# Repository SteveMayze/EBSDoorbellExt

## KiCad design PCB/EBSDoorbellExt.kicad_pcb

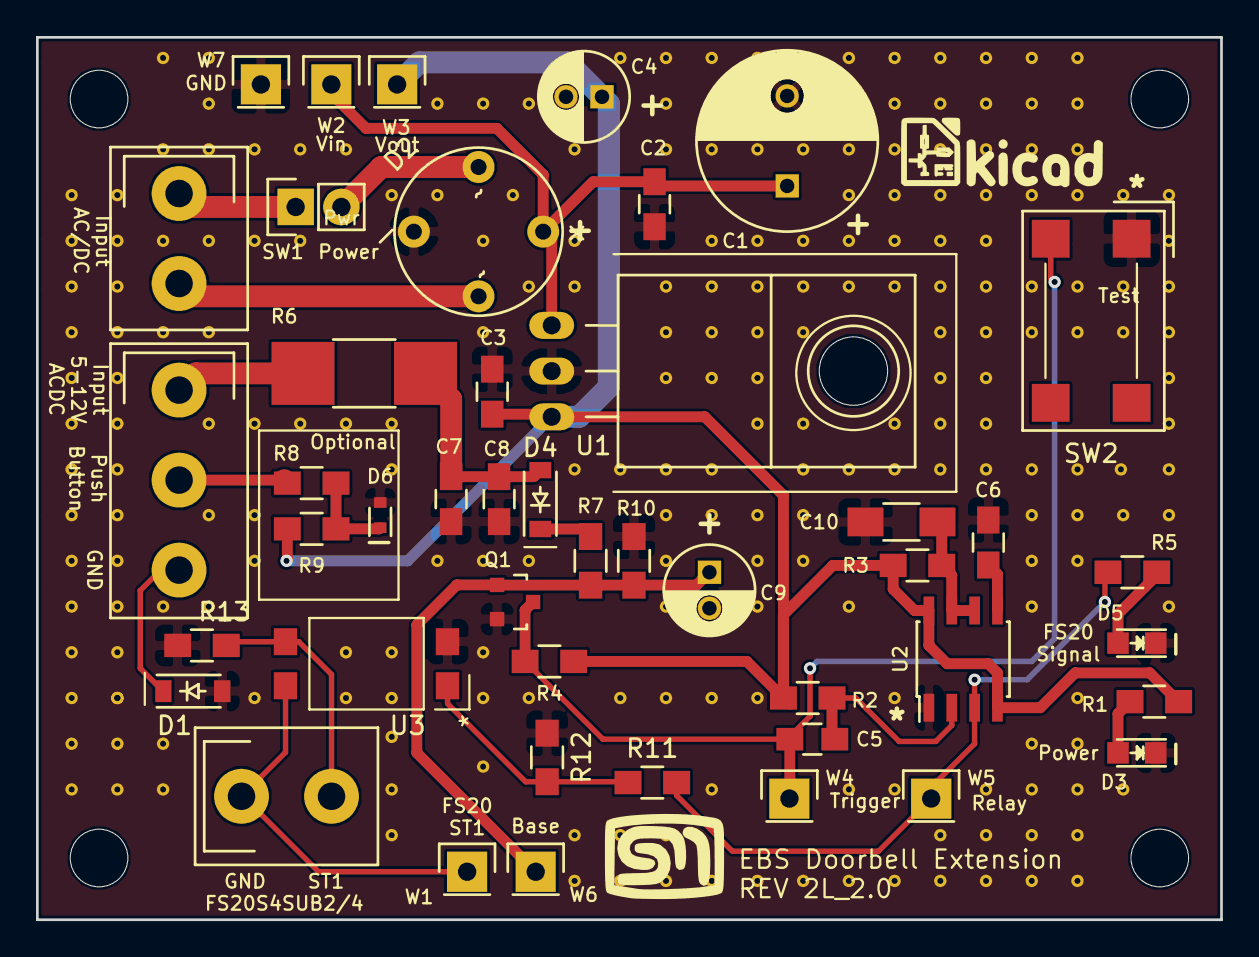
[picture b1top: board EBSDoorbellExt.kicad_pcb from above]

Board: 2 copper layers, 65.8 x 49.0 mm, 274 parts (0 on the bottom side), 23 nets.

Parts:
C1: 220μF; C_Radial_D10_L13_P5
C2, C6, C8: 100nF; C_0805_HandSoldering
C3: 100n; C_0805_HandSoldering
C4: 10μF; C_Radial_D5_L11_P2
C5: 1μF; C_0805_HandSoldering
C7: 10nF; C_0805_HandSoldering
C9: 1μF; C_Radial_D5_L11_P2
C10: 10μF; C_1206_HandSoldering
D1, D4: 1N4148W; SOD-123
D2: B80C1500G
D3: Pwr; LED_0805
D5: Signal; LED_0805
D6: PESD3V3S1UB; SOD-523
MOD1: FS20S4SUB2/4; BoardConnector_Horizontal_1x2_P5
P1: AC in; BoardConnector_Horizontal_1x2_P5
P2: Doorbell; BoardConnector_Horizontal_1x3_P5
Q1: BC846C; SOT-23
R1, R5, R8, R11: 1kΩ; R_0805_HandSoldering
R2, R3, R4, R7, R10: 100kΩ; R_0805_HandSoldering
R6: 1Ω; R_1812_HandSoldering
R9, R12: 10kΩ; R_0805_HandSoldering
R13: NOPOP; R_0805_HandSoldering
ST**14, ST**15, ST**16, ST**17, ST**18, ST**19, ST**24, ST**25, ST**26, ST**27, ST**28, ST**29, ST**31, ST**33, ST**35, ST**37, ST**41, ST**42, ST**43, ST**45, ST**47, ST**49, ST**53, ST**55, ST**59, ST**63, ST**65, ST**69, ST**73, ST**79, ST**84, ST**89, ST**92, ST**94, ST**102, ST**104, ST**105, ST**107, ST**110, ST**111, ST**112, ST**112#2, ST**113, ST**114, ST**115, ST**116, ST**116#2, ST**117, ST**123, ST**125, ST**126, ST**131, ST**141, ST**142, ST**143, ST**146, ST**147, ST**148, ST**151, ST**152, ST**153, ST**155, ST**156, ST**157, ST**158, ST**161, ST**162, ST**163, ST**165, ST**166, ST**167, ST**168, ST**169, ST**171, ST**173, ST**175, ST**176, ST**177, ST**179, ST**181, ST**182, ST**183, ST**184, ST**185, ST**186, ST**191, ST**192, ST**193, ST**194, ST**195, ST**196, ST**199, ST**201, ST**202, ST**203, ST**204, ST**205, ST**206, ST**207, ST**208, ST**209, ST**210, ST**211, ST**211#2, ST**212, ST**212#2, ST**213, ST**213#2, ST**214, ST**215, ST**215#2, ST**216, ST**216#2, ST**216#3, ST**216#4, ST**217, ST**218, ST**219, ST**221, ST**222, ST**223, ST**224, ST**226, ST**227, ST**231, ST**232, ST**233, ST**234, ST**236, ST**237, ST**244, ST**246, ST**247, ST**254, ST**255, ST**256, ST**257, ST**258, ST**259, ST**313, ST**411, ST**413, ST**511, ST**512, ST**810, ST**912, ST**1012, ST**1014, ST**1015, ST**1112, ST**1115, ST**1210, ST**1218, ST**1219, ST**1310, ST**1315, ST**1318, ST**1319, ST**1410, ST**1411, ST**1412, ST**1413, ST**1415, ST**1418, ST**1419, ST**1510, ST**1511, ST**1513, ST**1515, ST**1517, ST**1519, ST**1611, ST**1612, ST**1613, ST**1615, ST**1619, ST**1710, ST**1711, ST**1712, ST**1719, ST**1810, ST**1813, ST**1817, ST**1819, ST**1910, ST**1915, ST**1917, ST**1919, ST**2010, ST**2018, ST**2019, ST**2110, ST**2111, ST**2112, ST**2117, ST**2118, ST**2119, ST**2210, ST**2211, ST**2212, ST**2213, ST**2216, ST**2217, ST**2218, ST**2219, ST**2310, ST**2310#2, ST**2310#3, ST**2310#4, ST**2315, ST**2316, ST**2317, ST**2318, ST**2319, ST**2411, ST**2417, ST**2510, ST**2511, ST**2513, ST**21711, ST**21711#2, ST**21711#3, ST**21711#4, ST**21711#5, ST**21712, ST**21712#2, ST**21712#3, ST**21712#4, ST**211111: Stitch_VIA
SW1: Power; Pin_Header_Straight_1x02
SW2: FSM2JSMAA
U1: LM7809CT; TO-220_Neutral123_Horizontal
U2: LM555N; SOIC-8_3.9x4.9mm_Pitch1.27mm
U3: LTV-817; LTV_817
W1: FS20_ST1; Pin_Header_Straight_1x01
W2: Vin; Pin_Header_Straight_1x01
W3: Vout; Pin_Header_Straight_1x01
W4: Trigger; Pin_Header_Straight_1x01
W5: Relay; Pin_Header_Straight_1x01
W6: Base; Pin_Header_Straight_1x01
W7: GND; Pin_Header_Straight_1x01

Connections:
/FS20_Sig: R5.1, R11.2, U2.3, W5.1
/In1: P1.1, SW1.1
/In2: D2.4, P1.2
/Vcc: C3.1, C4.1, R1.1, R2.1, R3.1, R4.2, R9.1, U1.3, U2.4, U2.8, W3.1
/~Trigger: C5.2, Q1.3, R4.1, SW2.3, W4.1
GND: C1.2, C2.2, C3.2, C4.2, C6.1, C7.2, C8.2, C9.2, C10.2, D1.2, D2.1, D3.1, D5.1, D6.2, Q1.2, R10.1, R12.2, R13.2, ST**14.1, ST**15.1, ST**16.1, ST**17.1, ST**18.1, ST**19.1, ST**24.1, ST**25.1, ST**26.1, ST**27.1, ST**28.1, ST**29.1, ST**31.1, ST**33.1, ST**35.1, ST**37.1, ST**41.1, ST**42.1, ST**43.1, ST**45.1, ST**47.1, ST**49.1, ST**53.1, ST**55.1, ST**59.1, ST**63.1, ST**65.1, ST**69.1, ST**73.1, ST**79.1, ST**84.1, ST**89.1, ST**92.1, ST**94.1, ST**102.1, ST**104.1, ST**105.1, ST**107.1, ST**110.1, ST**111.1, ST**112.1, ST**112#2.1, ST**113.1, ST**114.1, ST**115.1, ST**116.1, ST**116#2.1, ST**117.1, ST**123.1, ST**125.1, ST**126.1, ST**131.1, ST**141.1, ST**142.1, ST**143.1, ST**146.1, ST**147.1, ST**148.1, ST**151.1, ST**152.1, ST**153.1, ST**155.1, ST**156.1, ST**157.1, ST**158.1, ST**161.1, ST**162.1, ST**163.1, ST**165.1, ST**166.1, ST**167.1, ST**168.1, ST**169.1, ST**171.1, ST**173.1, ST**175.1, ST**176.1, ST**177.1, ST**179.1, ST**181.1, ST**182.1, ST**183.1, ST**184.1, ST**185.1, ST**186.1, ST**191.1, ST**192.1, ST**193.1, ST**194.1, ST**195.1, ST**196.1, ST**199.1, ST**201.1, ST**202.1, ST**203.1, ST**204.1, ST**205.1, ST**206.1, ST**207.1, ST**208.1, ST**209.1, ST**210.1, ST**211.1, ST**211#2.1, ST**212.1, ST**212#2.1, ST**213.1, ST**213#2.1, ST**214.1, ST**215.1, ST**215#2.1, ST**216.1, ST**216#2.1, ST**216#3.1, ST**216#4.1, ST**217.1, ST**218.1, ST**219.1, ST**221.1, ST**222.1, ST**223.1, ST**224.1, ST**226.1, ST**227.1, ST**231.1, ST**232.1, ST**233.1, ST**234.1, ST**236.1, ST**237.1, ST**244.1, ST**246.1, ST**247.1, ST**254.1, ST**255.1, ST**256.1, ST**257.1, ST**258.1, ST**259.1, ST**313.1, ST**411.1, ST**413.1, ST**511.1, ST**512.1, ST**810.1, ST**912.1, ST**1012.1, ST**1014.1, ST**1015.1, ST**1112.1, ST**1115.1, ST**1210.1, ST**1218.1, ST**1219.1, ST**1310.1, ST**1315.1, ST**1318.1, ST**1319.1, ST**1410.1, ST**1411.1, ST**1412.1, ST**1413.1, ST**1415.1, ST**1418.1, ST**1419.1, ST**1510.1, ST**1511.1, ST**1513.1, ST**1515.1, ST**1517.1, ST**1519.1, ST**1611.1, ST**1612.1, ST**1613.1, ST**1615.1, ST**1619.1, ST**1710.1, ST**1711.1, ST**1712.1, ST**1719.1, ST**1810.1, ST**1813.1, ST**1817.1, ST**1819.1, ST**1910.1, ST**1915.1, ST**1917.1, ST**1919.1, ST**2010.1, ST**2018.1, ST**2019.1, ST**2110.1, ST**2111.1, ST**2112.1, ST**2117.1, ST**2118.1, ST**2119.1, ST**2210.1, ST**2211.1, ST**2212.1, ST**2213.1, ST**2216.1, ST**2217.1, ST**2218.1, ST**2219.1, ST**2310.1, ST**2310#2.1, ST**2310#3.1, ST**2310#4.1, ST**2315.1, ST**2316.1, ST**2317.1, ST**2318.1, ST**2319.1, ST**2411.1, ST**2417.1, ST**2510.1, ST**2511.1, ST**2513.1, ST**21711.1, ST**21711#2.1, ST**21711#3.1, ST**21711#4.1, ST**21711#5.1, ST**21712.1, ST**21712#2.1, ST**21712#3.1, ST**21712#4.1, ST**211111.1, SW2.1, U1.2, U2.1, U3.2, W7.1
unnamed: C1.1, C2.1, D2.3, U1.1, W2.1
unnamed: C5.1, R2.2, U2.2
unnamed: C6.2, U2.5
unnamed: C7.1, C8.1, D4.2, R6.1
unnamed: C9.1, Q1.1, R7.1, R10.2, W6.1
unnamed: C10.1, R3.2, U2.6, U2.7
unnamed: D1.1, P2.3
unnamed: D2.2, SW1.2
unnamed: D3.2, R1.2
unnamed: D4.1, R7.2
unnamed: D5.2, R5.2
unnamed: D6.1, R8.1, R9.2
unnamed: MOD1.1, U3.4, W1.1
unnamed: MOD1.2, R13.1, U3.3
unnamed: P2.1, R6.2
unnamed: P2.2, R8.2
unnamed: R11.1, R12.1, U3.1

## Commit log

2016-06-05 Initial commit to start the repo
2016-06-05 Added the .gitignore
2016-06-05 Added schematic
2016-06-05 Completed the initial layout and Gerbers
2016-06-06 Updated the layout to include the heatsink
2016-06-07 Added some test points and moved the LEDs help with the casing
2016-06-13 Changed the layout to use an Optocoupler instead of a relay and generated Gerbers
2016-06-26 Corrected some footprint issues
2016-06-27 Added protection diode on ground for voltage sensing
2016-06-27 Added the LTSpice models and some docs
2016-07-24 Rev 2 gerbers and stensil order
2016-07-24 Added the BOM with the cost of goods
